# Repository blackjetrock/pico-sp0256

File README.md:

# Rp2040 Emulation of the SP0256-AL2 IC

Despite the name, this projects does not use the RP Pico. It is a PCB that has the footprint of the 28pin SP0256-AL2 IC. It plugs in to the same footprint as the IC and performs the functions that the IC does. Well, some of them:

1) Has allophones of the SP0256-AL2 as audio samples
2) Responds to the ALD signal falliung edge, latches the allophone nyumber and plays it.
3) Drives the LRQ line

It does not:
1) Handle an external ROM
2) Handle the play allohone on address line going to 1 mode.
   
This version of the code and PCB is designed to replace an SP0256-AL2 based psion organiser II speech adapter. It will need testing and adjusting in other uses.
It should be treated as a work in progress.

This project builds on the work of two other projects the first is here:

https://github.com/ExtremeElectronics/SP0256-AL2-Pico-Emulation-Detail

and contains code that drives the PWM to generate the audio from the phoneme data which is at this project:

https://www.cpcwiki.eu/index.php/SP0256_Allophones

These two projects have been combined and then added to in order to do the emulation of the SP0256 IC itself, such that it can be placed into the footprint of one of those ICs.

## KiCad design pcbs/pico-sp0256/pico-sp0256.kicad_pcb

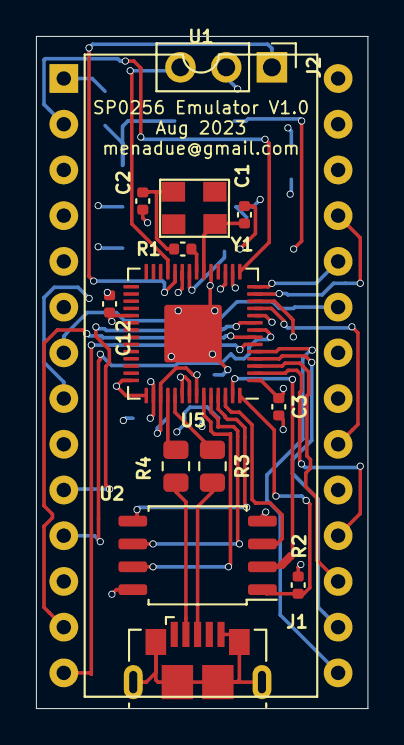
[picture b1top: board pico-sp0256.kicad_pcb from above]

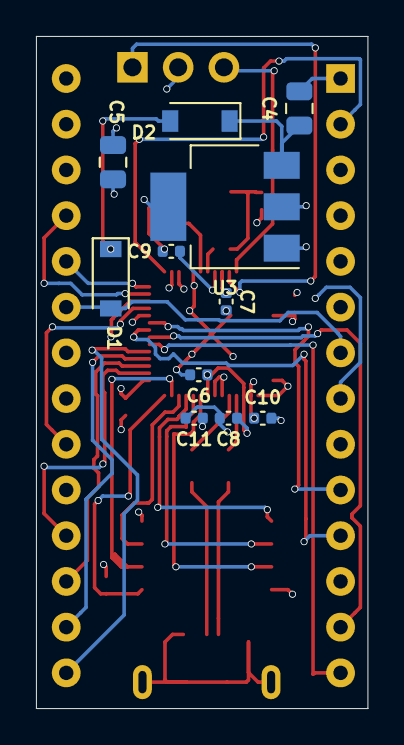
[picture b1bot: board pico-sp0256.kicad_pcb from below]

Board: 4 copper layers, 18.4 x 37.3 mm, 25 parts (11 on the bottom side), 36 nets.

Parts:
C1, C2: 27p; C_0402_1005Metric
C3, C6, C7, C9, C11, C12: 100n; C_0402_1005Metric
C4, C5: 10u; C_0805_2012Metric
C8, C10: 1u; C_0402_1005Metric
D1, D2: D_Small; D_SOD-123
J1: USB_B_Micro; USB_Micro-B_GCT_USB3076-30-A
J2: Conn_01x03_Female; PinHeader_1x03_P2.54mm_Vertical
R1: 1k; C_0402_1005Metric
R2: 10k; C_0402_1005Metric
R3, R4: 27R; R_0805_2012Metric
U1: SP0256AL2; DIP-28_W15.24mm
U2: W25Q128JVS; SOIC-8_5.23x5.23mm_P1.27mm
U3: NCP1117-3.3_SOT223; SOT-223-3_TabPin2
U5: RP2040; RP2040-QFN-56-no_holes
Y1: ABLS-12.000MHZ-B4-T; ecx-32

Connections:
+1V1: C6.1, C7.1, C8.1, U5.23, U5.45, U5.50
+3V3: C3.1, C5.1, C9.1, C10.1, C11.1, C12.1, R2.1, U2.8, U3.2, U5.1, U5.10, U5.22, U5.33, U5.42, U5.43, U5.44, U5.48, U5.49
GND: C1.2, C2.2, C3.2, C4.2, C5.2, C6.2, C7.2, C8.2, C9.2, C10.2, C11.2, C12.2, J1.5, J1.6, J2.2, U1.1, U2.4, U3.1, U5.19, U5.57
unnamed: C2.1, R1.2, Y1.2
unnamed: C4.1, D2.1, U3.3
unnamed: D1.1, D2.2
unnamed: J1.2, R4.2
unnamed: J1.3, R3.2
QSPI_SCLK: U2.6, U5.52
QSPI_SD0: U2.5, U5.53
QSPI_SD1: U2.2, U5.55
QSPI_SD2: U2.3, U5.54
QSPI_SD3: U2.7, U5.51
QSPI_SS: R2.2, U2.1, U5.56
SP_A1: U1.18, U5.2
SP_A2: U1.17, U5.3
SP_A3: U1.16, U5.4
SP_A4: U1.15, U5.5
SP_A5: U1.14, U5.6
SP_A6: U1.13, U5.7
SP_A7: U1.11, U5.8
SP_A8: U1.10, U5.9
SP_ALD: U1.20, U5.11
SP_DIGITAL_OUT: U1.24, U5.14
SP_LRQ_N: U1.9, U5.16
SP_RESET_N: U1.2, U5.15
SP_SBY: U1.8, U5.17
SP_SBY_RES_N: U1.25, U5.13
SP_SE: U1.19, U5.12
SWCLK: J2.1, U5.24
SWD: J2.3, U5.25
USB_DM: R4.1, U5.46
USB_DP: R3.1, U5.47
VDD: D1.2, U1.7, U1.23
XIN: C1.1, U5.20, Y1.1
XOUT: R1.1, U5.21

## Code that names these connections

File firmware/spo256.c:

/**
 * SPO256 -AL2 
 * samples from https://www.cpcwiki.eu/index.php/SP0256_Allophones
 * 
 * Pico code Derek Woodroffe 4/5/2022
 *
 */

//pico SDK includes
#include <stdio.h>
#include "pico/stdlib.h"
#include "hardware/pwm.h"
#include "pico/multicore.h"

//program includes
#include "allophones.c"
#include "allophoneDefs.h"

//must be pins on the same slice
#define soundIO1 11
#define soundIO2 12

#define PIN_SP_A1            0
#define PIN_SP_A2            1
#define PIN_SP_A3            2
#define PIN_SP_A4            3
#define PIN_SP_A5            4
#define PIN_SP_A6            5
#define PIN_SP_A7            6
#define PIN_SP_A8            7
#define PIN_SP_ALD           8
#define PIN_SP_SE            9
#define PIN_SP_SBY_RES_N    10
#define PIN_SP_DIGITAL_OUT  11
#define PIN_SP_RESET_N      12
#define PIN_SP_LRQ_N        13
#define PIN_SP_SBY          14


#define rate 90

uint PWMslice;

void PlayAllophone(int al)
{
  int b,s;
  uint8_t v;
  
  s=allophonesizeCorrected[al];
  //printf("\nstart %d", s);
  
  for(b=0;b<s;b++)
    {
      v=allophoneindex[al][b]; //get delta value
      //printf("\n%d", v);
      
      pwm_set_both_levels(PWMslice,v,v);
      volatile int x;

      for(x=0; x<125*9; x++)
	{
	}
      
      //sleep_us(rate);
      //sleep_ms(2);
    }

  //printf("\nend");
}

void PlayAllophones(uint8_t *alist,int listlength)
{
  int a;

  printf("\nStart allophones");
  for(a=0; a<listlength; a++)
    {
      PlayAllophone(alist[a]);
    }

  pwm_set_both_levels(PWMslice, 0x0, 0x0);
}

void SetPWM(void)
{
  gpio_init(soundIO1);
  gpio_set_dir(soundIO1,GPIO_OUT);
  gpio_set_function(soundIO1, GPIO_FUNC_PWM);
  
  //  gpio_init(soundIO2);
  //gpio_set_dir(soundIO2,GPIO_OUT);
  //gpio_set_function(soundIO2, GPIO_FUNC_PWM);
  
  PWMslice=pwm_gpio_to_slice_num (soundIO1);
  
  pwm_set_clkdiv(PWMslice,16);
  pwm_set_both_levels(PWMslice,0x80,0x80);
  
  pwm_set_output_polarity(PWMslice,true,false);
  
  pwm_set_wrap (PWMslice, 256);
  pwm_set_enabled(PWMslice,true);
  
}

void test_gpios(void)
{
  gpio_init(soundIO1);
  gpio_set_dir(soundIO1,GPIO_OUT);

  while(1)
    {
      gpio_put(soundIO1, 0);
      sleep_ms(2);
      gpio_put(soundIO1, 1);
      sleep_ms(2);
      
    }
  

}

void test_gpios2(void)
{
  SetPWM();
  
  while(1)
    {
      pwm_set_both_levels(PWMslice,0x10,0x10);
      //      gpio_put(soundIO1, 0);
      sleep_ms(2);
      pwm_set_both_levels(PWMslice,0xA0,0xA0);
      //gpio_put(soundIO1, 1);
      sleep_ms(2);
      
    }
}

void core1_main(void)
{
  uint8_t alist[] ={AR,PA5,PP,EH,IY,PA5,TT2,WH,EH,EH,NN1,PA2,PA3,TT2,IY,PA5,FF,OR,PA3,TT2,IY,PA5};

  //  printf("\nCore1 started");

  int last_ald = gpio_get(PIN_SP_ALD);
  int ald;

  //  irq_set_mask_enabled(0xffffffff, false);

      
  while(0)
    {
      printf("\nPlaying %d", sizeof(alist));
      
      PlayAllophones(alist,sizeof(alist));


    }

  while(1)
    {
      // Sit in loop waiting for allophone selection
      ald = gpio_get(PIN_SP_ALD);

      if( (ald == 0) && (last_ald == 1) )
	{
	  //	  printf("\nNeg edge");

	  // When we get a neg edge we lath the address lines in
	  int gpio_states = (sio_hw->gpio_in) & 0x3F;

	  //printf("\nAllophone %d", gpio_states);

	  gpio_put(PIN_SP_LRQ_N, 1);
	  gpio_put(PIN_SP_SBY, 0);

	  PlayAllophone(gpio_states);
	  
	  gpio_put(PIN_SP_LRQ_N, 0);
	  gpio_put(PIN_SP_SBY, 1);
	}

      last_ald = ald;
    }

  while(1)
    {
      printf("\nPlaying %d", sizeof(alist));
      
      PlayAllophones(alist,sizeof(alist));

      sleep_ms(3000);

    }
}

void set_gpio_input(int gpio)
{
  gpio_init(gpio);
  gpio_set_dir(gpio, GPIO_IN);
}

int main()
{
  ////////////////////////////////////////////////////////////////////////////////
  //
  // Overclock as needed
  //
  ////////////////////////////////////////////////////////////////////////////////
#if 0  
  #define OVERCLOCK 135000
  //#define OVERCLOCK 200000
  //#define OVERCLOCK 270000
  //#define OVERCLOCK 360000
  
#if OVERCLOCK > 270000
  /* Above this speed needs increased voltage */
  vreg_set_voltage(VREG_VOLTAGE_1_20);
  sleep_ms(1000);
#endif

  
  /* Overclock */
  set_sys_clock_khz( OVERCLOCK, 1 );
#endif
  
  stdio_init_all();
  //  sleep_ms(2000);

  printf("\n*********************");
  printf("\n*  SP0256 Emulator  *");
  printf("\n*********************");
  
  set_gpio_input(PIN_SP_A1);
  set_gpio_input(PIN_SP_A2);
  set_gpio_input(PIN_SP_A3);
  set_gpio_input(PIN_SP_A4);
  set_gpio_input(PIN_SP_A5);
  set_gpio_input(PIN_SP_A6);
  set_gpio_input(PIN_SP_A7);
  set_gpio_input(PIN_SP_A8);
  
  
  gpio_init(PIN_SP_LRQ_N);
  gpio_set_dir(PIN_SP_LRQ_N, GPIO_OUT);
  gpio_put(PIN_SP_LRQ_N, 0);

  gpio_init(PIN_SP_SBY);
  gpio_set_dir(PIN_SP_SBY, GPIO_OUT);
  gpio_put(PIN_SP_SBY, 1);
  
  SetPWM();
  //test_gpios2();
  
  uint8_t alist[] ={HH,EH,LL,AX,OW,PA5,WW,OR,LL,DD1};

#if 1
  multicore_launch_core1(core1_main);
#else
    
  while(1)
    {
      printf("\nPlaying %d", sizeof(alist));
      
      PlayAllophones(alist,sizeof(alist));

      sleep_ms(3000);

    }
  
#endif
  while(1)
    {
    }
  
}
